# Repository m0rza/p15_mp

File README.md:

# 15 Keys Custom Macropad

More to come :)

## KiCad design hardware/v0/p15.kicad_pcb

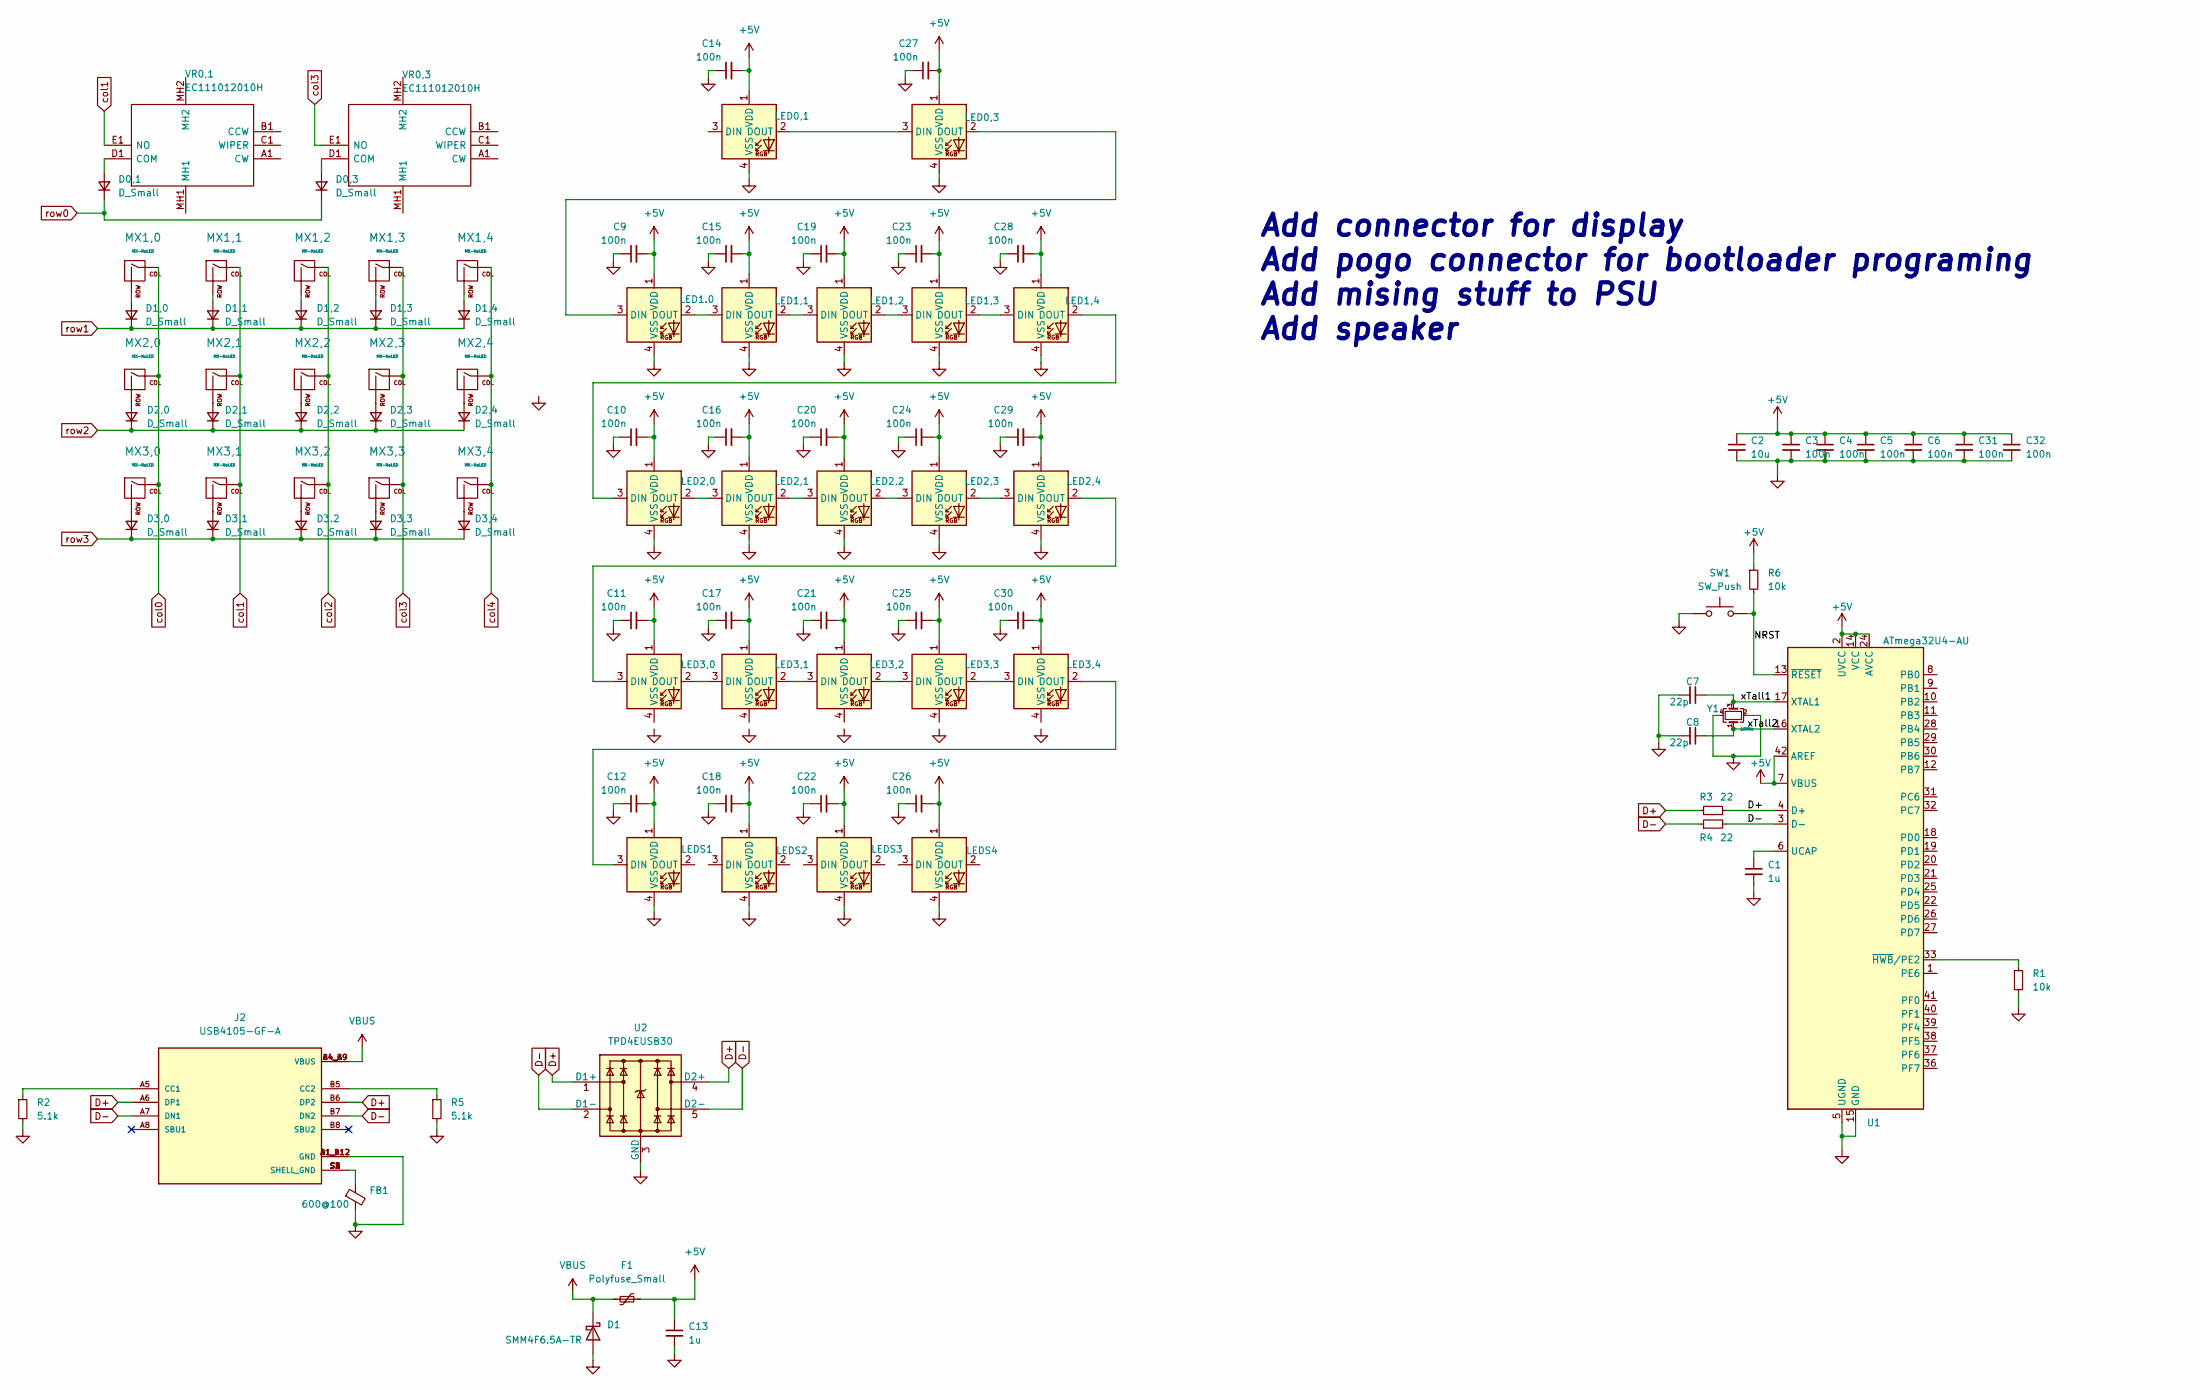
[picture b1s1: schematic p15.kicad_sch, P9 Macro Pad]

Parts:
C1, C13: 1u; C_0805_2012Metric_Pad1.18x1.45mm_HandSolder
C2: 10u; C_0805_2012Metric_Pad1.18x1.45mm_HandSolder
C3, C4, C5, C6, C9, C10, C11, C12, C14, C15, C16, C17, C18, C19, C20, C21, C22, C23, C24, C25, C26, C27, C28, C29, C30, C31, C32: 100n; C_0805_2012Metric_Pad1.18x1.45mm_HandSolder
C7, C8: 22p; C_0805_2012Metric_Pad1.18x1.45mm_HandSolder
D0,1, D0,3, D1,0, D1,1, D1,2, D1,3, D1,4, D2,0, D2,1, D2,2, D2,3, D2,4, D3,0, D3,1, D3,3, D3,4, D3.2: D_Small; D_SOD-123
D1: SMM4F6.5A-TR
F1: Polyfuse_Small; RESC3216X125N
FB1: 600@100
J2: USB4105-GF-A; GCT_USB4105-GF-A; PARTREV A3
LED0,1, LED0,3, LED1,1, LED1,2, LED1,3, LED1,4, LED1.0, LED2,0, LED2,1, LED2,2, LED2,3, LED2,4, LED3,0, LED3,1, LED3,2, LED3,3, LED3,4: MX_SK6812MINI-E; LED_MX_6028R
LEDS1, LEDS2, LEDS3, LEDS4: MX_SK6812MINI-E; LED_MX_6028R
MX1,0, MX1,1, MX1,2, MX1,3, MX1,4, MX2,0, MX2,1, MX2,2, MX2,3, MX2,4, MX3,0, MX3,1, MX3,2, MX3,3, MX3,4: MX-NoLED; MXOnly-1U-Hotswap-Antishear
R1, R6: 10k; R_0805_2012Metric_Pad1.20x1.40mm_HandSolder
R2, R5: 5.1k; R_0805_2012Metric_Pad1.20x1.40mm_HandSolder
R3, R4: 22; R_0805_2012Metric_Pad1.20x1.40mm_HandSolder
SW1: SW_Push; SW_PTS525SM15SMTR2LFS
U1: ATmega32U4-AU; TQFP-44_10x10mm_P0.8mm
U2: TPD4EUSB30; USON-10_2.5x1.0mm_P0.5mm
VR0,1, VR0,3: EC111012010H; Mouser Part Number 688-EC111012010H
Y1: 16MHz; OSCCC320X250X60N

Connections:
+5V: C2.1, C3.1, C4.1, C5.1, C6.1, C9.2, C10.2, C11.2, C12.2, C13.1, C14.2, C15.2, C16.2, C17.2, C18.2, C19.2, C20.2, C21.2, C22.2, C23.2, C24.2, C25.2, C26.2, C27.2, C28.2, C29.2, C30.2, C31.1, C32.1, F1.1, LED0,1.1 (VDD), LED0,3.1 (VDD), LED1,1.1 (VDD), LED1,2.1 (VDD), LED1,3.1 (VDD), LED1,4.1 (VDD), LED1.0.1 (VDD), LED2,0.1 (VDD), LED2,1.1 (VDD), LED2,2.1 (VDD), LED2,3.1 (VDD), LED2,4.1 (VDD), LED3,0.1 (VDD), LED3,1.1 (VDD), LED3,2.1 (VDD), LED3,3.1 (VDD), LED3,4.1 (VDD), LEDS1.1 (VDD), LEDS2.1 (VDD), LEDS3.1 (VDD), LEDS4.1 (VDD), R6.1, U1.2 (UVCC), U1.7 (VBUS), U1.14 (VCC), U1.24 (AVCC), U1.34 (VCC), U1.42 (AREF), U1.44 (AVCC)
/NRST: R6.2, SW1.2, U1.13 (~RESET)
/xTall1: C7.1, U1.17 (XTAL1), Y1.3
/xTall2: C8.1, U1.16 (XTAL2), Y1.1
D+: J2.A6 (DP1), J2.B6 (DP2), R3.1, R3.2, U1.4 (D+), U2.1 (D1+), U2.4 (D2+)
D-: J2.A7 (DN1), J2.B7 (DN2), R4.1, R4.2, U1.3 (D-), U2.2 (D1-), U2.5 (D2-)
GND: C1.2, C2.2, C3.2, C4.2, C5.2, C6.2, C7.2, C8.2, C9.1, C10.1, C11.1, C12.1, C13.2, C14.1, C15.1, C16.1, C17.1, C18.1, C19.1, C20.1, C21.1, C22.1, C23.1, C24.1, C25.1, C26.1, C27.1, C28.1, C29.1, C30.1, C31.2, C32.2, D1.2 (A), FB1.2, J2.A1_B12 (GND), J2.B1_A12 (GND), LED0,1.4 (VSS), LED0,3.4 (VSS), LED1,1.4 (VSS), LED1,2.4 (VSS), LED1,3.4 (VSS), LED1,4.4 (VSS), LED1.0.4 (VSS), LED2,0.4 (VSS), LED2,1.4 (VSS), LED2,2.4 (VSS), LED2,3.4 (VSS), LED2,4.4 (VSS), LEDS1.4 (VSS), LEDS2.4 (VSS), LEDS3.4 (VSS), LEDS4.4 (VSS), R1.2, R2.2, R5.2, SW1.1, U1.5 (UGND), U1.15 (GND), U1.23 (GND), U1.35 (GND), U1.43 (GND), U2.3 (GND), U2.8 (GND), Y1.2, Y1.4
unnamed: C1.1, U1.6 (UCAP)
unnamed: D0,1.2 (A), VR0,1.D1 (COM)
unnamed: D0,3.2 (A), VR0,3.D1 (COM)
unnamed: D1,0.2 (A), MX1,0.2 (ROW)
unnamed: D1,1.2 (A), MX1,1.2 (ROW)
unnamed: D1,2.2 (A), MX1,2.2 (ROW)
unnamed: D1,3.2 (A), MX1,3.2 (ROW)
unnamed: D1,4.2 (A), MX1,4.2 (ROW)
unnamed: D2,0.2 (A), MX2,0.2 (ROW)
unnamed: D2,1.2 (A), MX2,1.2 (ROW)
unnamed: D2,2.2 (A), MX2,2.2 (ROW)
unnamed: D2,3.2 (A), MX2,3.2 (ROW)
unnamed: D2,4.2 (A), MX2,4.2 (ROW)
unnamed: D3,0.2 (A), MX3,0.2 (ROW)
unnamed: D3,1.2 (A), MX3,1.2 (ROW)
unnamed: D3,3.2 (A), MX3,3.2 (ROW)
unnamed: D3,4.2 (A), MX3,4.2 (ROW)
unnamed: D3.2.2 (A), MX3,2.2 (ROW)
unnamed: FB1.1, J2.S1 (SHELL_GND), J2.S2 (SHELL_GND), J2.S3 (SHELL_GND), J2.S4 (SHELL_GND)
unnamed: J2.A5 (CC1), R2.1
unnamed: J2.B5 (CC2), R5.1
unnamed: LED0,1.2 (DOUT), LED0,3.3 (DIN)
unnamed: LED0,3.2 (DOUT), LED1.0.3 (DIN)
unnamed: LED1,1.2 (DOUT), LED1,2.3 (DIN)
unnamed: LED1,1.3 (DIN), LED1.0.2 (DOUT)
unnamed: LED1,2.2 (DOUT), LED1,3.3 (DIN)
unnamed: LED1,3.2 (DOUT), LED1,4.3 (DIN)
unnamed: LED1,4.2 (DOUT), LED2,0.3 (DIN)
unnamed: LED2,0.2 (DOUT), LED2,1.3 (DIN)
unnamed: LED2,1.2 (DOUT), LED2,2.3 (DIN)
unnamed: LED2,2.2 (DOUT), LED2,3.3 (DIN)
unnamed: LED2,3.2 (DOUT), LED2,4.3 (DIN)
unnamed: LED2,4.2 (DOUT), LED3,0.3 (DIN)
unnamed: LED3,0.2 (DOUT), LED3,1.3 (DIN)
unnamed: LED3,1.2 (DOUT), LED3,2.3 (DIN)
unnamed: LED3,2.2 (DOUT), LED3,3.3 (DIN)
unnamed: LED3,3.2 (DOUT), LED3,4.3 (DIN)
unnamed: LED3,4.2 (DOUT), LEDS1.3 (DIN)
unnamed: R1.1, U1.33 (~HWB/PE2)
VBUS: D1.1 (K), F1.2, J2.A4_B9 (VBUS), J2.B4_A9 (VBUS)
col0: MX1,0.1 (COL), MX2,0.1 (COL), MX3,0.1 (COL)
col1: MX1,1.1 (COL), MX2,1.1 (COL), MX3,1.1 (COL), VR0,1.E1 (NO)
col2: MX1,2.1 (COL), MX2,2.1 (COL), MX3,2.1 (COL)
col3: MX1,3.1 (COL), MX2,3.1 (COL), MX3,3.1 (COL), VR0,3.E1 (NO)
col4: MX1,4.1 (COL), MX2,4.1 (COL), MX3,4.1 (COL)
row0: D0,1.1 (K), D0,3.1 (K)
row1: D1,0.1 (K), D1,1.1 (K), D1,2.1 (K), D1,3.1 (K), D1,4.1 (K)
row2: D2,0.1 (K), D2,1.1 (K), D2,2.1 (K), D2,3.1 (K), D2,4.1 (K)
row3: D3,0.1 (K), D3,1.1 (K), D3,3.1 (K), D3,4.1 (K), D3.2.1 (K)

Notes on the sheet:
Add connector for display Add pogo connector for bootloader programing Add mising stuff to PSU Add speaker

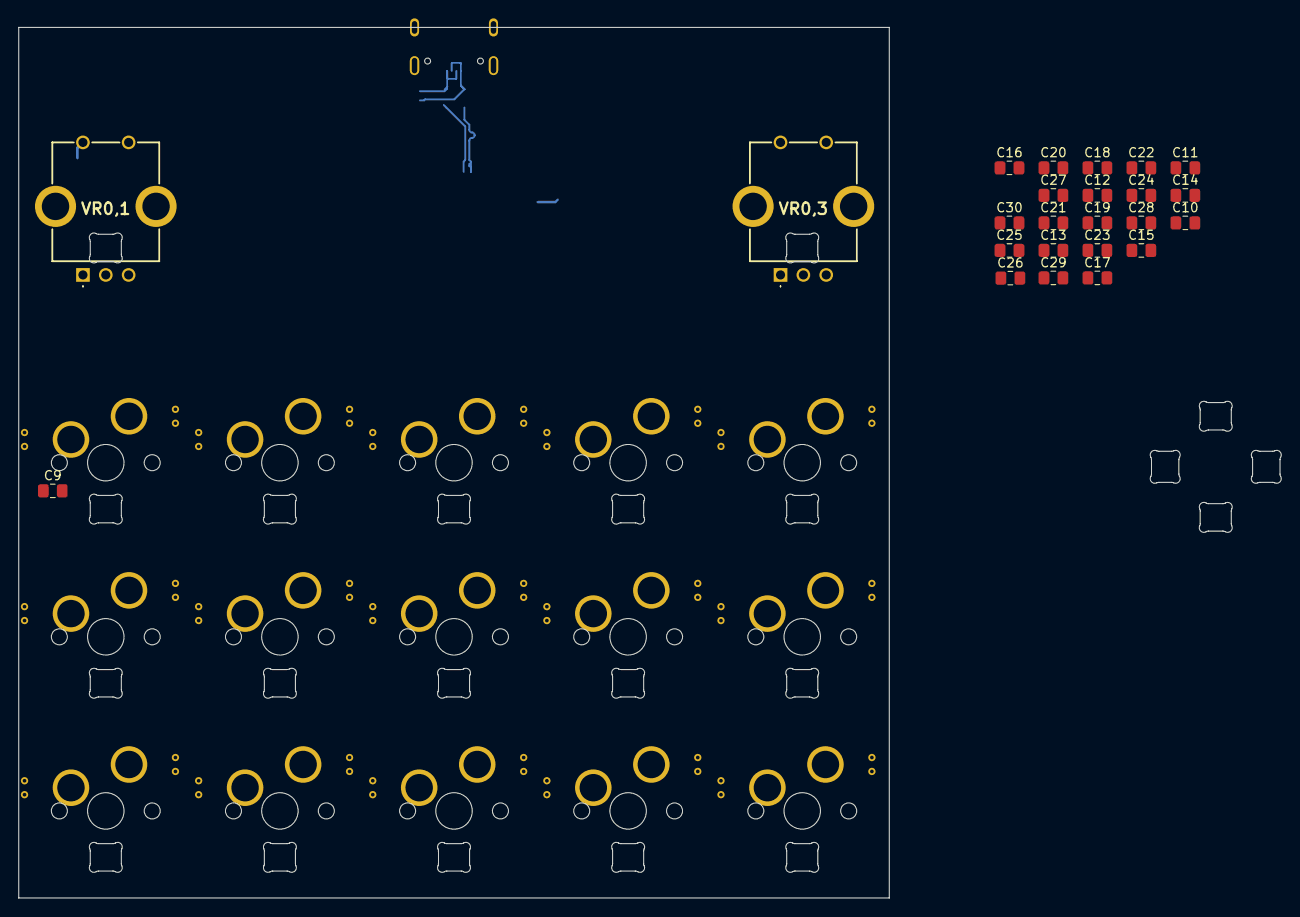
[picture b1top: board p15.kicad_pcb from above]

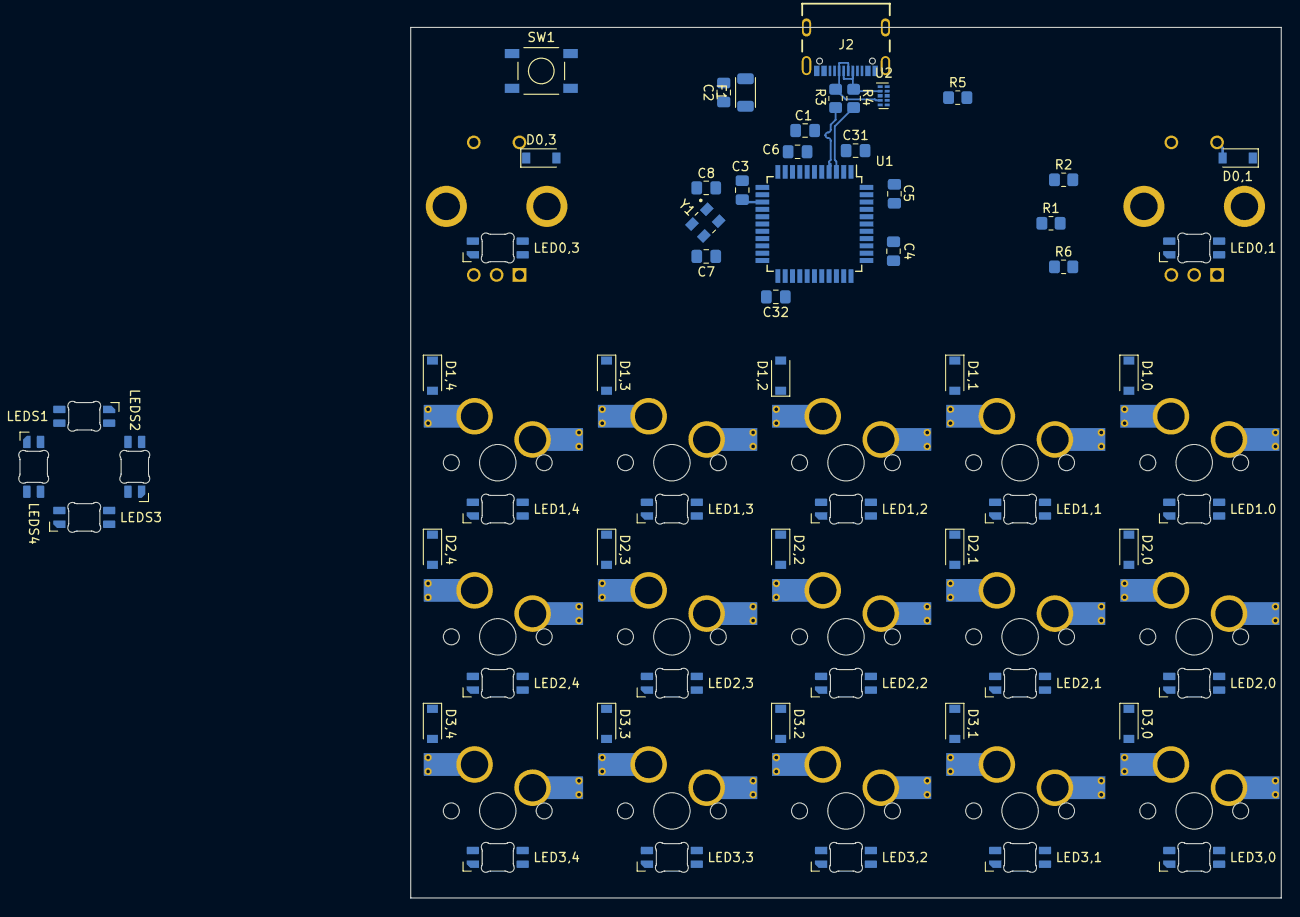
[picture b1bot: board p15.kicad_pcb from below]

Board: 2 copper layers, 138.1 x 95.2 mm, 99 parts (60 on the bottom side), 56 nets.

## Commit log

2022-08-17 move things around
2022-08-17 Conect crystal
2022-08-17 routed crytal
2022-08-17 more routing
2023-01-11 last changes not sure what
